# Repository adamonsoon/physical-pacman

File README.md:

# Physical Pacman

Physical Pacman is an in-progress project meant to create a clone of the classic Pacman game, which runs on a board powered by electromagnets. Once we reach the finish line, more comprehensive documentation will be provided.

In the project files you will find the materials needed to create your own physical Pacman clone, as well as a coil winding machine.
To complete the project you will have to either print and build the coil winding machine, or use an existing one.

If you do attempt to wind the required 230+ coils manually, please send us a video :)

Using our machine, it would take approx 11-15 hours to wind all the coils once you are proficient at operating the machine.

Project ToDo:
* Get 100% of relays connected.
* Add code to toggle shift-register/pin mixed output and map it to board.
* Integration testing and fine tuning.

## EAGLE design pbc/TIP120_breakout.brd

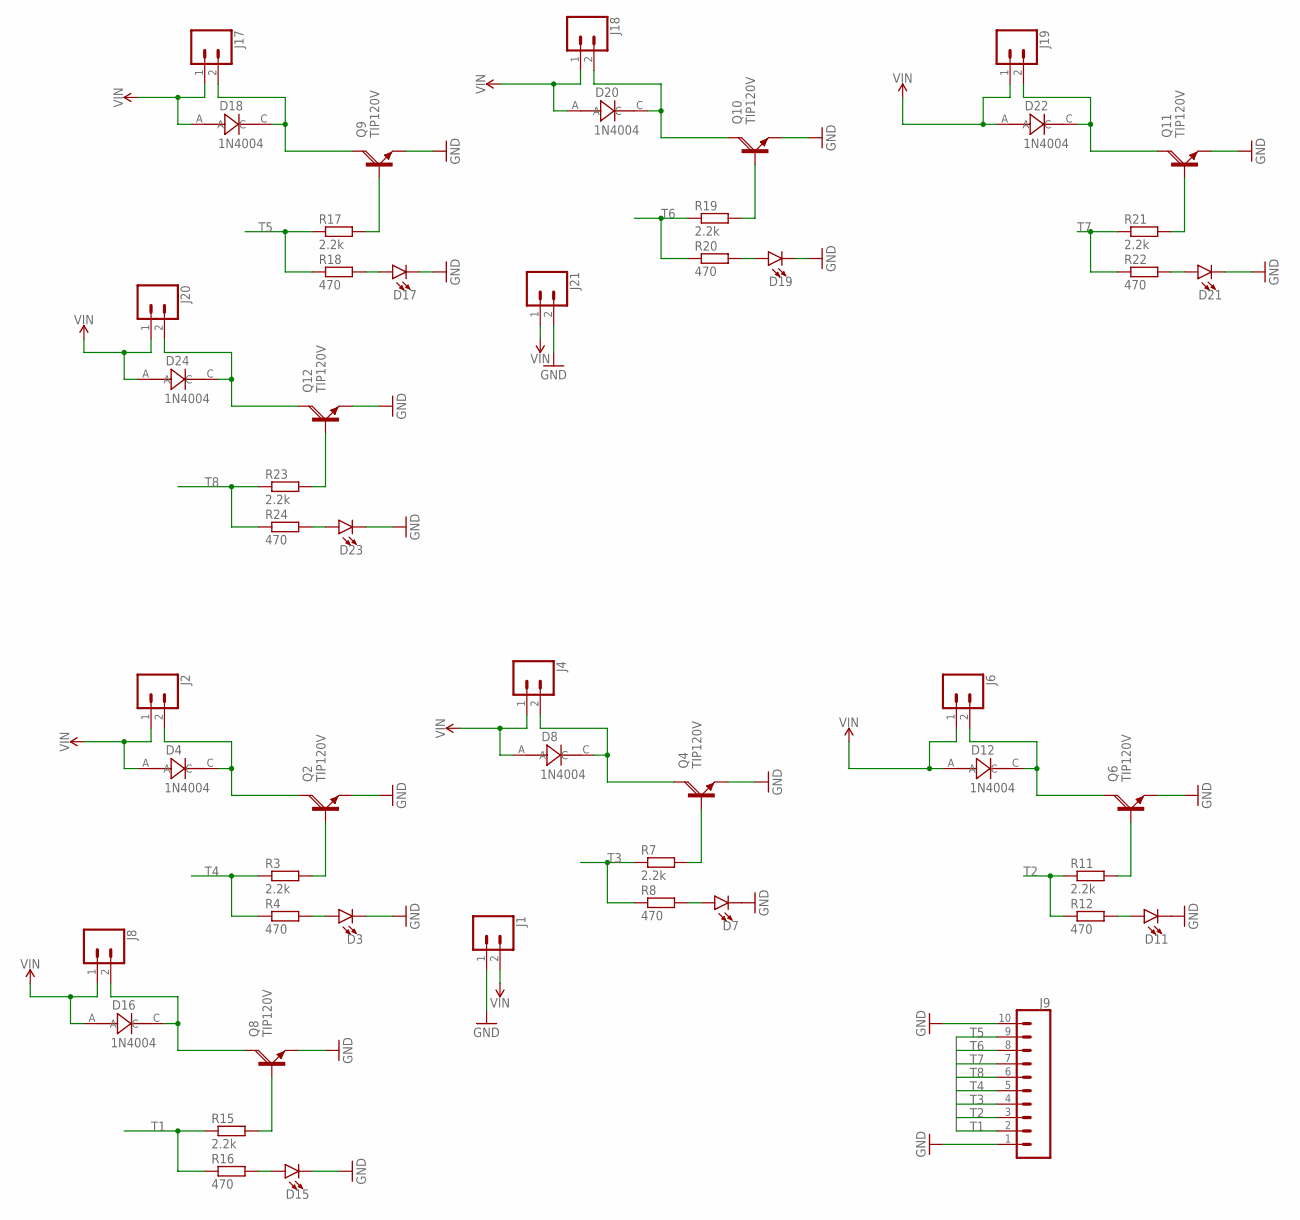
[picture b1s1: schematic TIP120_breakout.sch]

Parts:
D3, D7, D11, D15, D17, D19, D21, D23: LED3MM; LED_3MM
D4, D8, D12, D16, D18, D20, D22, D24: 1N4004; 1N4004_DIOAD520W79L463D238
J1, J2, J4, J6, J8, J17, J18, J19, J20, J21: CONN_025MM; SCREWTERMINAL-5MM-2
J9: CONN_10"; 1X10
Q2, Q4, Q6, Q8, Q9, Q10, Q11, Q12: TIP120V; TO220AV
R3, R7, R11, R15, R17, R19, R21, R23: 2.2k; 0207/7
R4, R8, R12, R16, R18, R20, R22, R24: 470; 0207/7

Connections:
GND: D3.K (C), D7.K (C), D11.K (C), D15.K (C), D17.K (C), D19.K (C), D21.K (C), D23.K (C), J1.1, J9.1, J9.10, J21.2, Q2.E, Q4.E, Q6.E, Q8.E, Q9.E, Q10.E, Q11.E, Q12.E
unnamed: Q2.B, R3.2
unnamed: D3.A, R4.2
unnamed: D4.C, J2.2, Q2.C
unnamed: Q4.B, R7.2
unnamed: D7.A, R8.2
unnamed: D8.C, J4.2, Q4.C
unnamed: Q6.B, R11.2
unnamed: D11.A, R12.2
unnamed: D12.C, J6.2, Q6.C
unnamed: Q8.B, R15.2
unnamed: D15.A, R16.2
unnamed: D16.C, J8.2, Q8.C
unnamed: Q9.B, R17.2
unnamed: D17.A, R18.2
unnamed: D18.C, J17.2, Q9.C
unnamed: Q10.B, R19.2
unnamed: D19.A, R20.2
unnamed: D20.C, J18.2, Q10.C
unnamed: Q11.B, R21.2
unnamed: D21.A, R22.2
unnamed: D22.C, J19.2, Q11.C
unnamed: Q12.B, R23.2
unnamed: D23.A, R24.2
unnamed: D24.C, J20.2, Q12.C
T1: J9.2, R15.1, R16.1
T2: J9.3, R11.1, R12.1
T3: J9.4, R7.1, R8.1
T4: J9.5, R3.1, R4.1
T5: J9.9, R17.1, R18.1
T6: J9.8, R19.1, R20.1
T7: J9.7, R21.1, R22.1
T8: J9.6, R23.1, R24.1
VIN: D4.A, D8.A, D12.A, D16.A, D18.A, D20.A, D22.A, D24.A, J1.2, J2.1, J4.1, J6.1, J8.1, J17.1, J18.1, J19.1, J20.1, J21.1

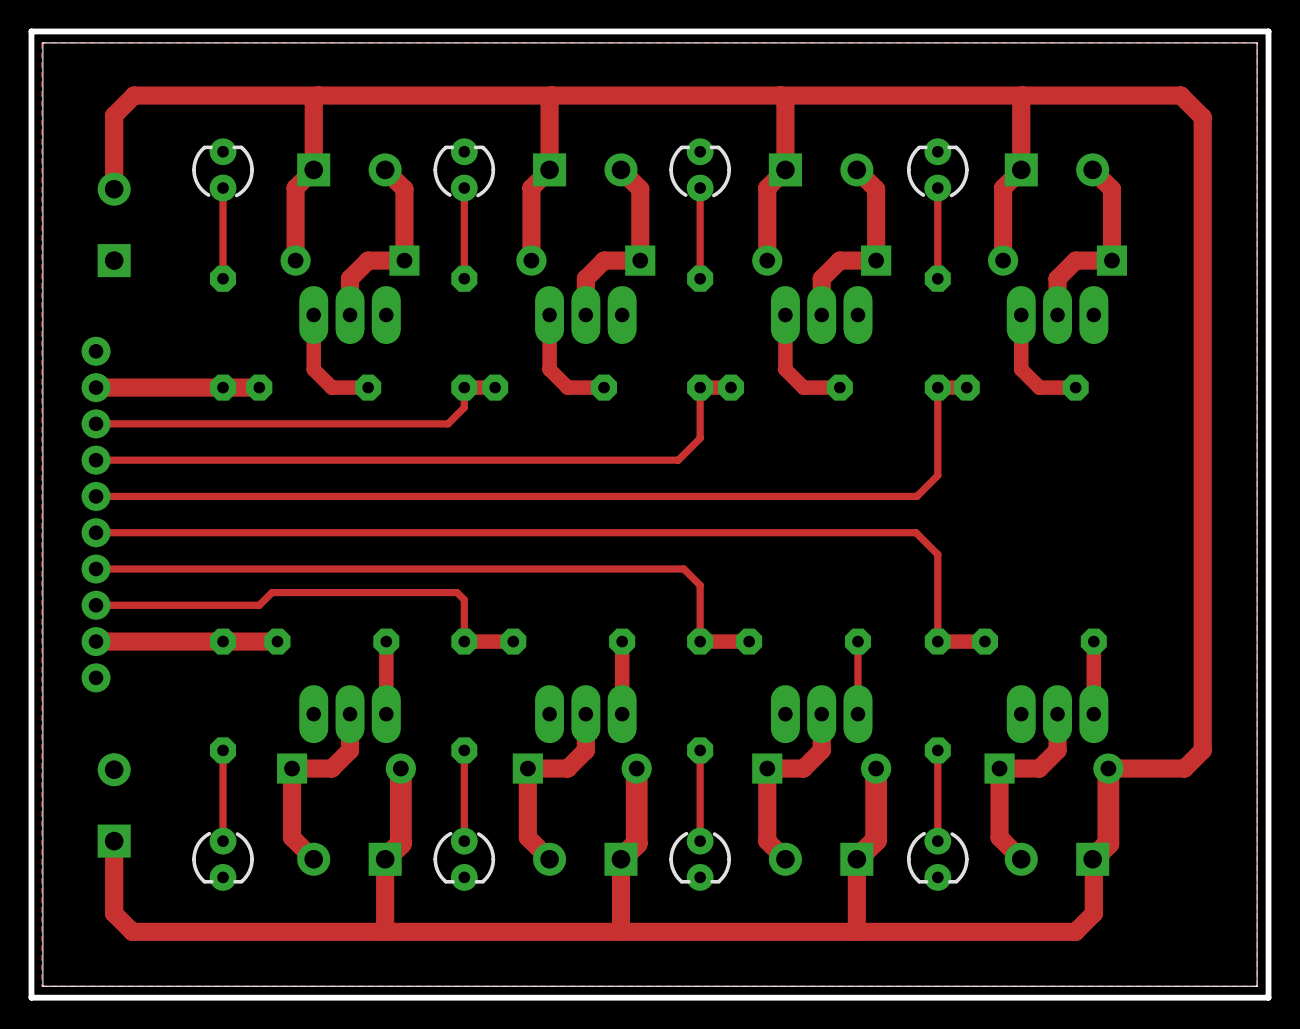
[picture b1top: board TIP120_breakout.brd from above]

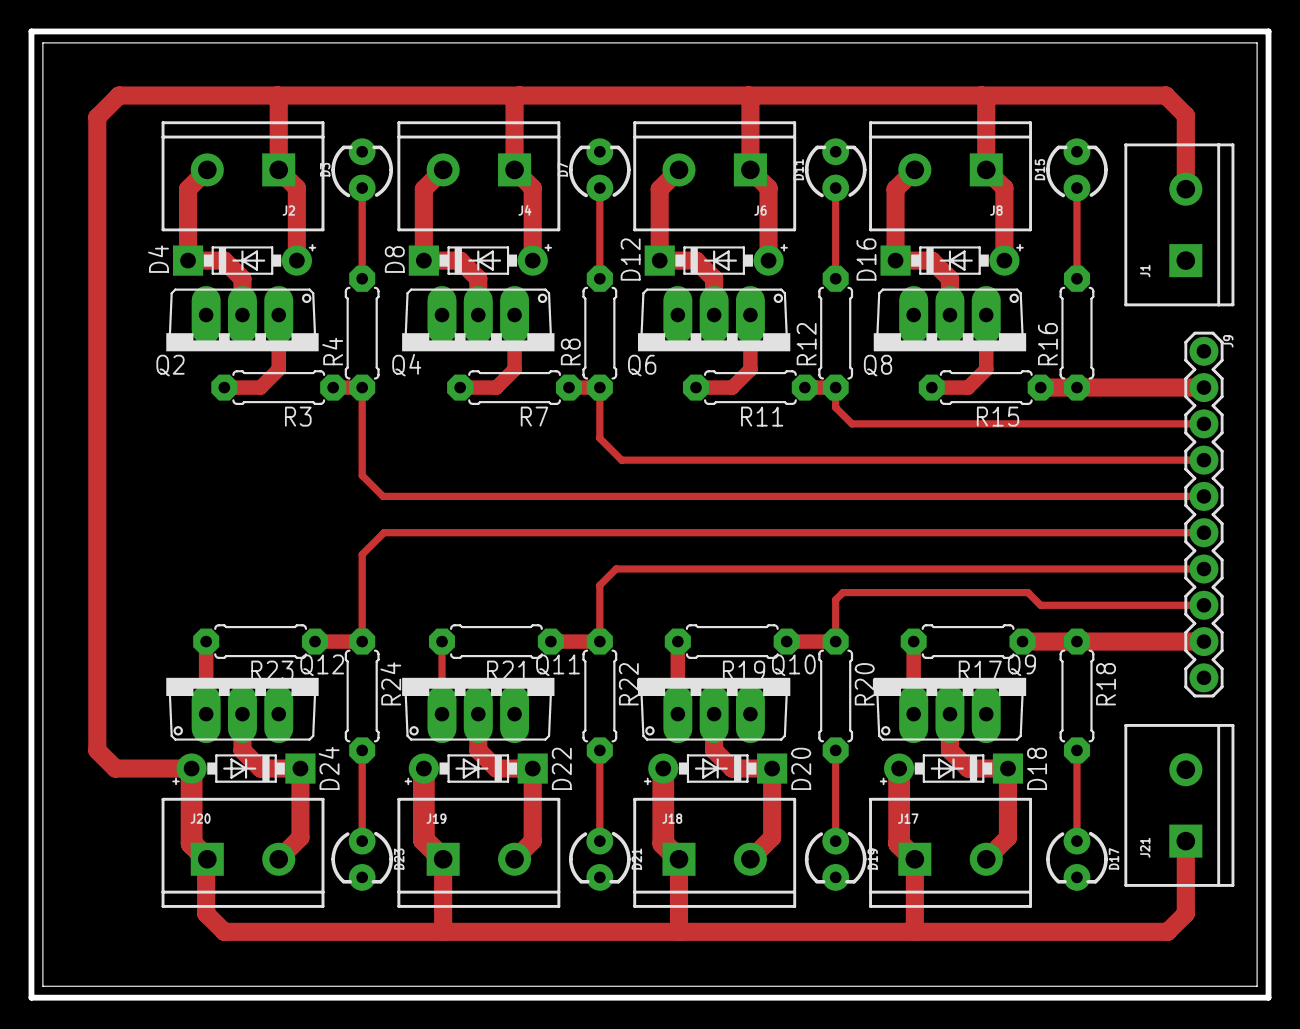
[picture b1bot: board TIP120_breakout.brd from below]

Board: 2 copper layers, 86.6 x 67.6 mm, 51 parts (51 on the bottom side), 34 nets.

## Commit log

2017-09-07 first batch of files
2017-09-10 re-organize project, add code
2017-09-11 added scheduler, tests, some refactoring
2017-09-15 add mp3 files
2017-09-15 added rf
2017-09-15 hackathon, no time for small commits
2017-09-15 added pacman servo, improved rfMaster
2017-09-16 BlinkyController complete
2017-09-17 refactor to lower memory usage
